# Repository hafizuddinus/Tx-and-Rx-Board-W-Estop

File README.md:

link schematic and layout of tx and rx board:
- tx schematic    : https://kicanvas.org/?repo=https%3A%2F%2Fgithub.com%2Fhafizuddinus%2FTx-and-Rx-Board-W-Estop%2Fblob%2Fmain%2FTx-Board.kicad_sch
- rx layout       : https://kicanvas.org/?repo=https%3A%2F%2Fgithub.com%2Fhafizuddinus%2FTx-and-Rx-Board-W-Estop%2Fblob%2Fmain%2FTx-Board-Copy.kicad_pcb
- rx schematic    : https://kicanvas.org/?repo=https%3A%2F%2Fgithub.com%2Fhafizuddinus%2FTx-and-Rx-Board-W-Estop%2Fblob%2Fmain%2FRx_Board-Copy.kicad_sch
- rx layout       : https://kicanvas.org/?repo=https%3A%2F%2Fgithub.com%2Fhafizuddinus%2FTx-and-Rx-Board-W-Estop%2Fblob%2Fmain%2FRx_Board-Copy.kicad_pcb

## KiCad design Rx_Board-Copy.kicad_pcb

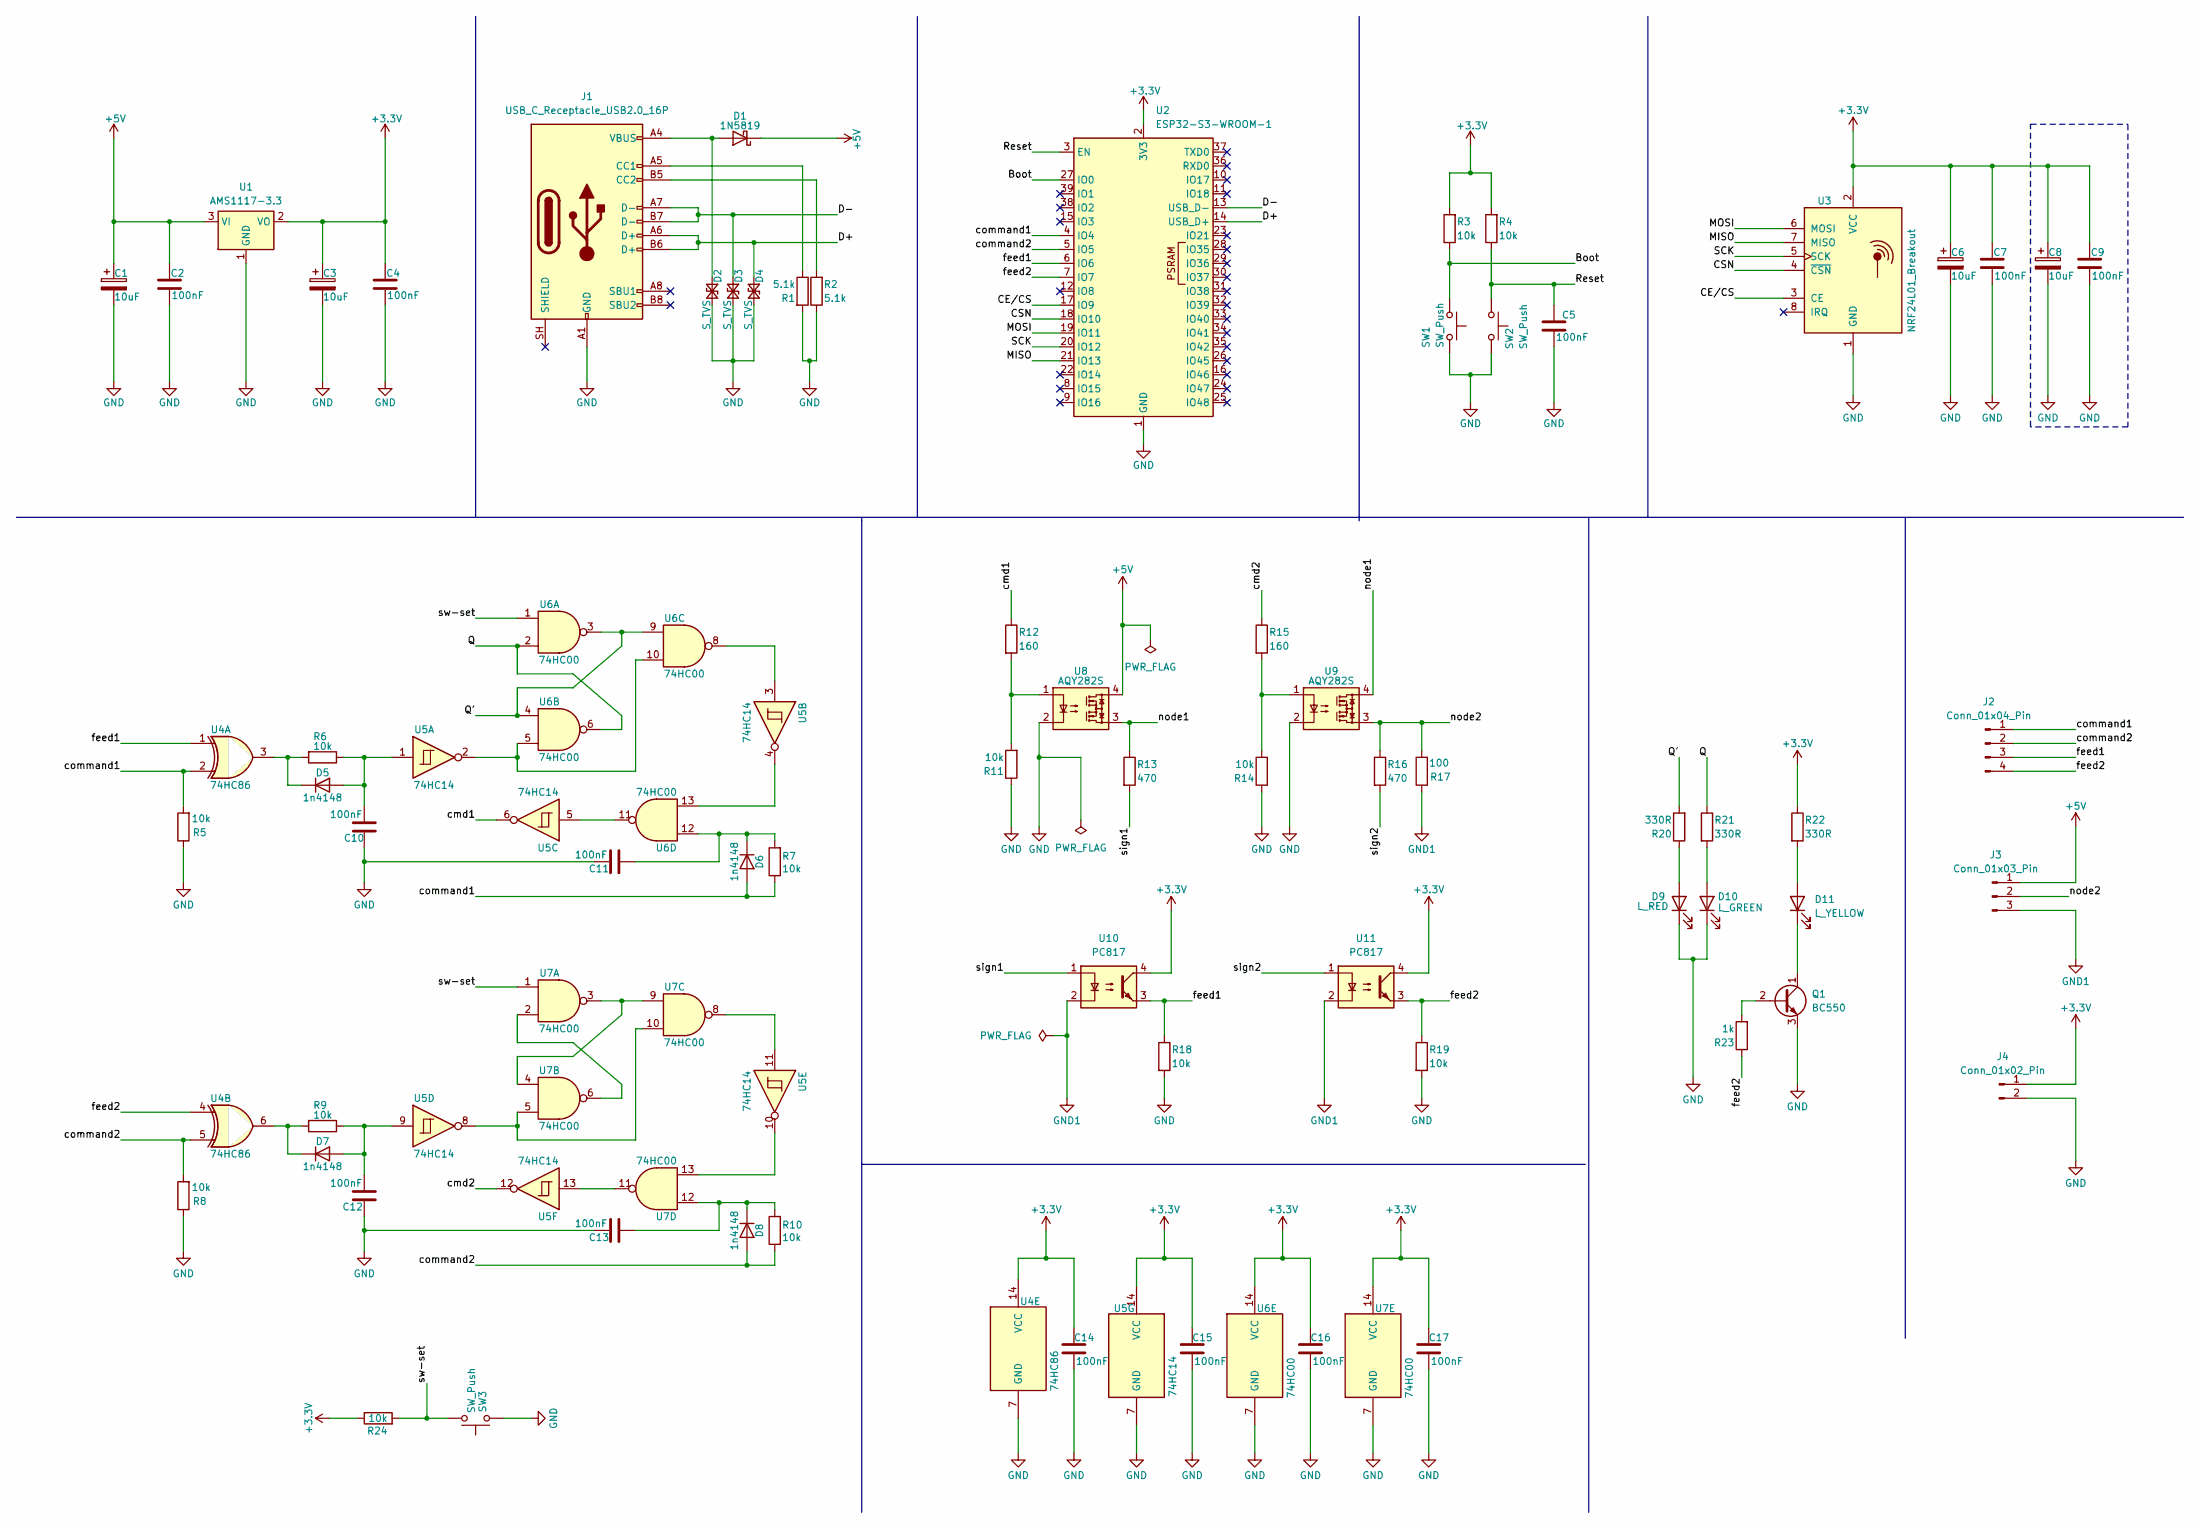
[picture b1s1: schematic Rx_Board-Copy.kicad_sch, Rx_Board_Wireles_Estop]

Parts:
C1, C3, C6, C8: 10uF; C_0805_2012Metric
C2, C4, C5, C7, C9, C10, C11, C12, C13, C14, C15, C16, C17: 100nF; C_0805_2012Metric
D1: 1N5819; D_SOD-123
D2, D3, D4: S_TVS; D_SOD-323
D5, D6, D7, D8: 1n4148; D_0805_2012Metric
D9: L_RED; LED_0805_2012Metric
D10: L_GREEN; LED_0805_2012Metric
D11: L_YELLOW; LED_0805_2012Metric
J1: USB_C_Receptacle_USB2.0_16P; USB_C_Receptacle_HRO_TYPE-C-31-M-12
J2: Conn_01x04_Pin; JST_EH_B4B-EH-A_1x04_P2.50mm_Vertical
J3: Conn_01x03_Pin; TerminalBlock_Phoenix_MKDS-1,5-3-5.08_1x03_P5.08mm_Horizont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
J4: Conn_01x02_Pin; JST_EH_S2B-EH_1x02_P2.50mm_Horizontal
Q1: BC550; TO-92_Inline
R1, R2: 5.1k; R_0805_2012Metric
R3, R4, R5, R6, R7, R8, R9, R10, R11, R14, R18, R19, R24: 10k; R_0805_2012Metric
R12, R15: 160; R_0805_2012Metric
R13, R16: 470; R_0805_2012Metric
R17: 100; R_0805_2012Metric
R20, R21, R22: 330R; R_0805_2012Metric
R23: 1k; R_0805_2012Metric
SW1, SW2: SW_Push; SW_Push_SPST_NO_Alps_SKRK
SW3: SW_Push; SW_Push_1P1T_NO_CK_KMR2
U1: AMS1117-3.3; SOT-223-3_TabPin2
U2: ESP32-S3-WROOM-1
U3: NRF24L01_Breakout; nRF24L01_Breakout
U4: 74HC86; SOIC-14_3.9x8.7mm_P1.27mm
U5: 74HC14; SOIC-14_3.9x8.7mm_P1.27mm
U6, U7: 74HC00; SOIC-14_3.9x8.7mm_P1.27mm
U8, U9: AQY282S; SO-4_4.4x4.3mm_P2.54mm
U10, U11: PC817; DIP-4_W7.62mm

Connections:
+3.3V: C3.1, C4.2, C6.1, C7.2, C8.1, C9.2, C14.2, C15.2, C16.2, C17.2, J4.1, R3.2, R4.2, R22.1, R24.1, U1.2 (VO), U2.2 (3V3), U3.2 (VCC), U4.14 (VCC), U5.14 (VCC), U6.14 (VCC), U7.14 (VCC), U10.4, U11.4
+5V: C1.1, C2.2, D1.1 (K), J3.1, U1.3 (VI), U8.4
/Boot: R3.1, SW1.1, U2.27 (IO0)
/CE/CS: U2.17 (IO9), U3.3 (CE)
/CSN: U2.18 (IO10), U3.4 (~CSN)
/D+: D4.1 (A1), J1.A6 (D+), J1.B6 (D+), U2.14 (USB_D+)
/D-: D3.1 (A1), J1.A7 (D-), J1.B7 (D-), U2.13 (USB_D-)
/MISO: U2.21 (IO13), U3.7 (MISO)
/MOSI: U2.19 (IO11), U3.6 (MOSI)
/Q: R21.1, U6.2, U6.6
/Q': R20.2, U6.3, U6.4, U6.9
/Reset: C5.2, R4.1, SW2.1, U2.3 (EN)
/SCK: U2.20 (IO12), U3.5 (SCK)
/cmd1: R12.1, U5.6
/cmd2: R15.1, U5.12
/command1: D6.2 (A), J2.1, R5.2, R7.1, U2.4 (IO4), U4.2
/command2: D8.2 (A), J2.2, R8.2, R10.1, U2.5 (IO5), U4.5
/feed1: J2.3, R18.1, U2.6 (IO6), U4.1, U10.3
/feed2: J2.4, R19.1, R23.1, U2.7 (IO7), U4.4, U11.3
/node1: R13.1, U8.3, U9.4
/node2: J3.2, R16.1, R17.2, U9.3
/sign1: R13.2, U10.1
/sign2: R16.2, U11.1
/sw-set: R24.2, SW3.2, U6.1, U7.1
GND: C1.2, C2.1, C3.2, C4.1, C5.1, C6.2, C7.1, C8.2, C9.1, C10.2, C11.2, C12.2, C13.2, C14.1, C15.1, C16.1, C17.1, D2.2 (A2), D3.2 (A2), D4.2 (A2), D9.1 (K), D10.1 (K), J1.A1 (GND), J1.A12 (GND), J1.B1 (GND), J1.B12 (GND), J4.2, Q1.3 (E), R1.2, R2.1, R5.1, R8.1, R11.1, R14.1, R18.2, R19.2, SW1.2, SW2.2, SW3.1, U1.1 (GND), U2.1 (GND), U2.40 (GND), U2.41 (GND), U3.1 (GND), U4.7 (GND), U5.7 (GND), U6.7 (GND), U7.7 (GND), U8.2, U9.2
GND1: J3.3, R17.1, U10.2, U11.2
unnamed: D1.2 (A), D2.1 (A1), J1.A4 (VBUS), J1.A9 (VBUS), J1.B4 (VBUS), J1.B9 (VBUS)
unnamed: C10.1, D5.2 (A), R6.1, U5.1
unnamed: D5.1 (K), R6.2, U4.3
unnamed: C11.1, D6.1 (K), R7.2, U6.12
unnamed: C12.1, D7.2 (A), R9.1, U5.9
unnamed: D7.1 (K), R9.2, U4.6
unnamed: C13.1, D8.1 (K), R10.2, U7.12
unnamed: D9.2 (A), R20.1
unnamed: D10.2 (A), R21.2
unnamed: D11.2 (A), R22.2
unnamed: D11.1 (K), Q1.1 (C)
unnamed: J1.A5 (CC1), R1.1
unnamed: J1.B5 (CC2), R2.2
unnamed: Q1.2 (B), R23.2
unnamed: R11.2, R12.2, U8.1
unnamed: R14.2, R15.2, U9.1
unnamed: U5.2, U6.5, U6.10
unnamed: U5.3, U6.8
unnamed: U5.4, U6.13
unnamed: U5.5, U6.11
unnamed: U5.8, U7.5, U7.10
unnamed: U5.10, U7.13
unnamed: U5.11, U7.8
unnamed: U5.13, U7.11
unnamed: U7.2, U7.6
unnamed: U7.3, U7.4, U7.9

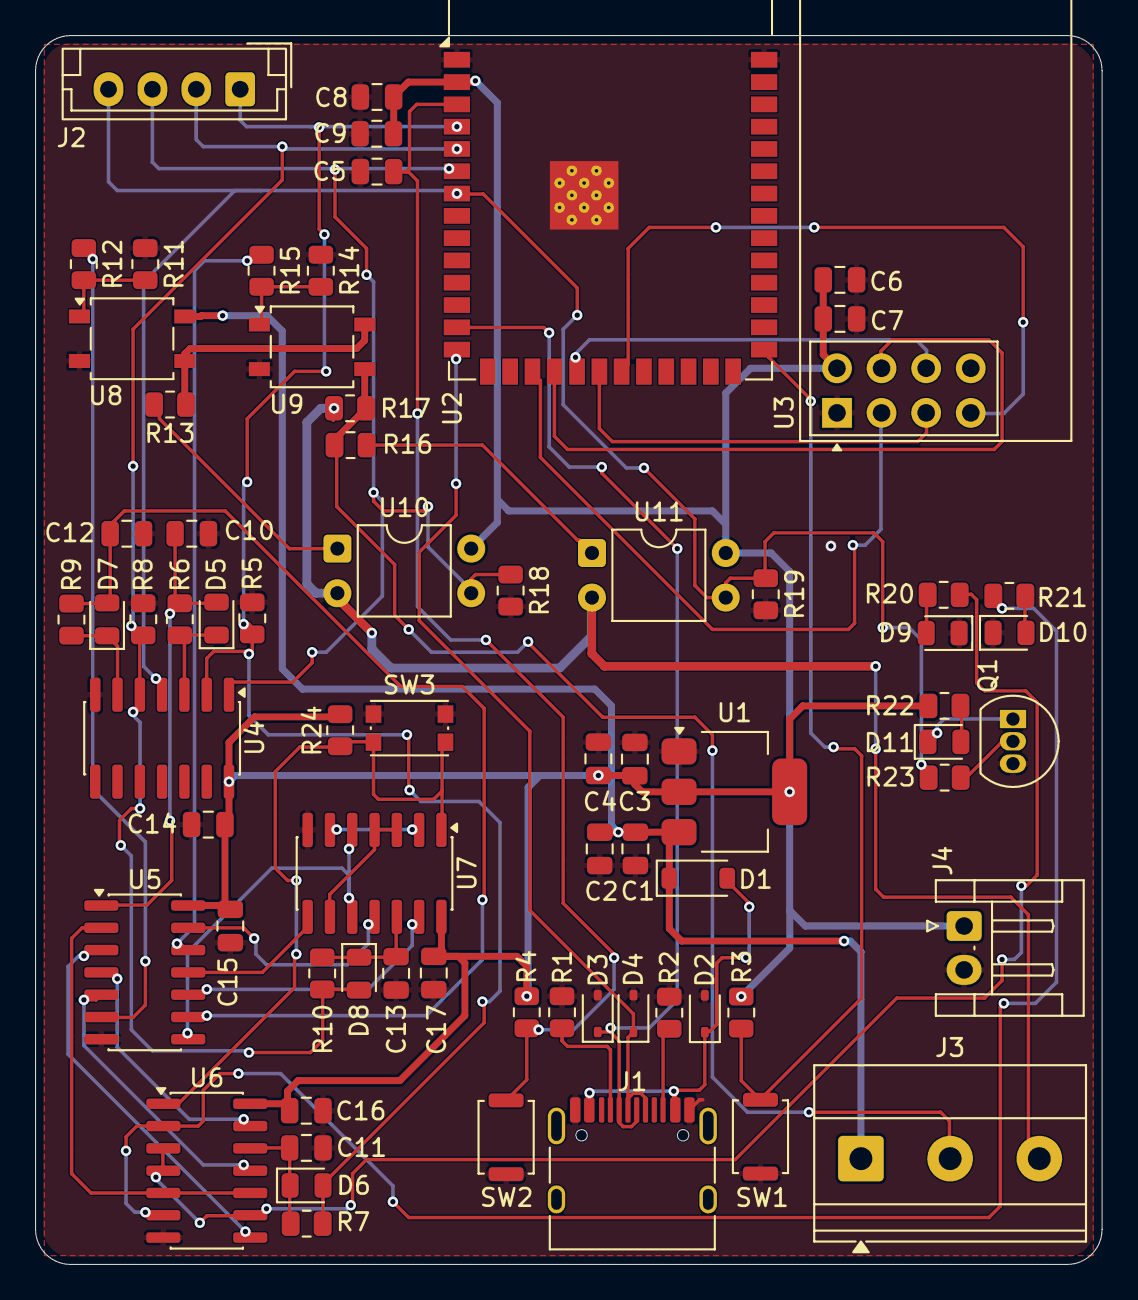
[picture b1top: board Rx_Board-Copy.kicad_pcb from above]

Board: 2 copper layers, 60.8 x 70.0 mm, 71 parts (0 on the bottom side), 52 nets.

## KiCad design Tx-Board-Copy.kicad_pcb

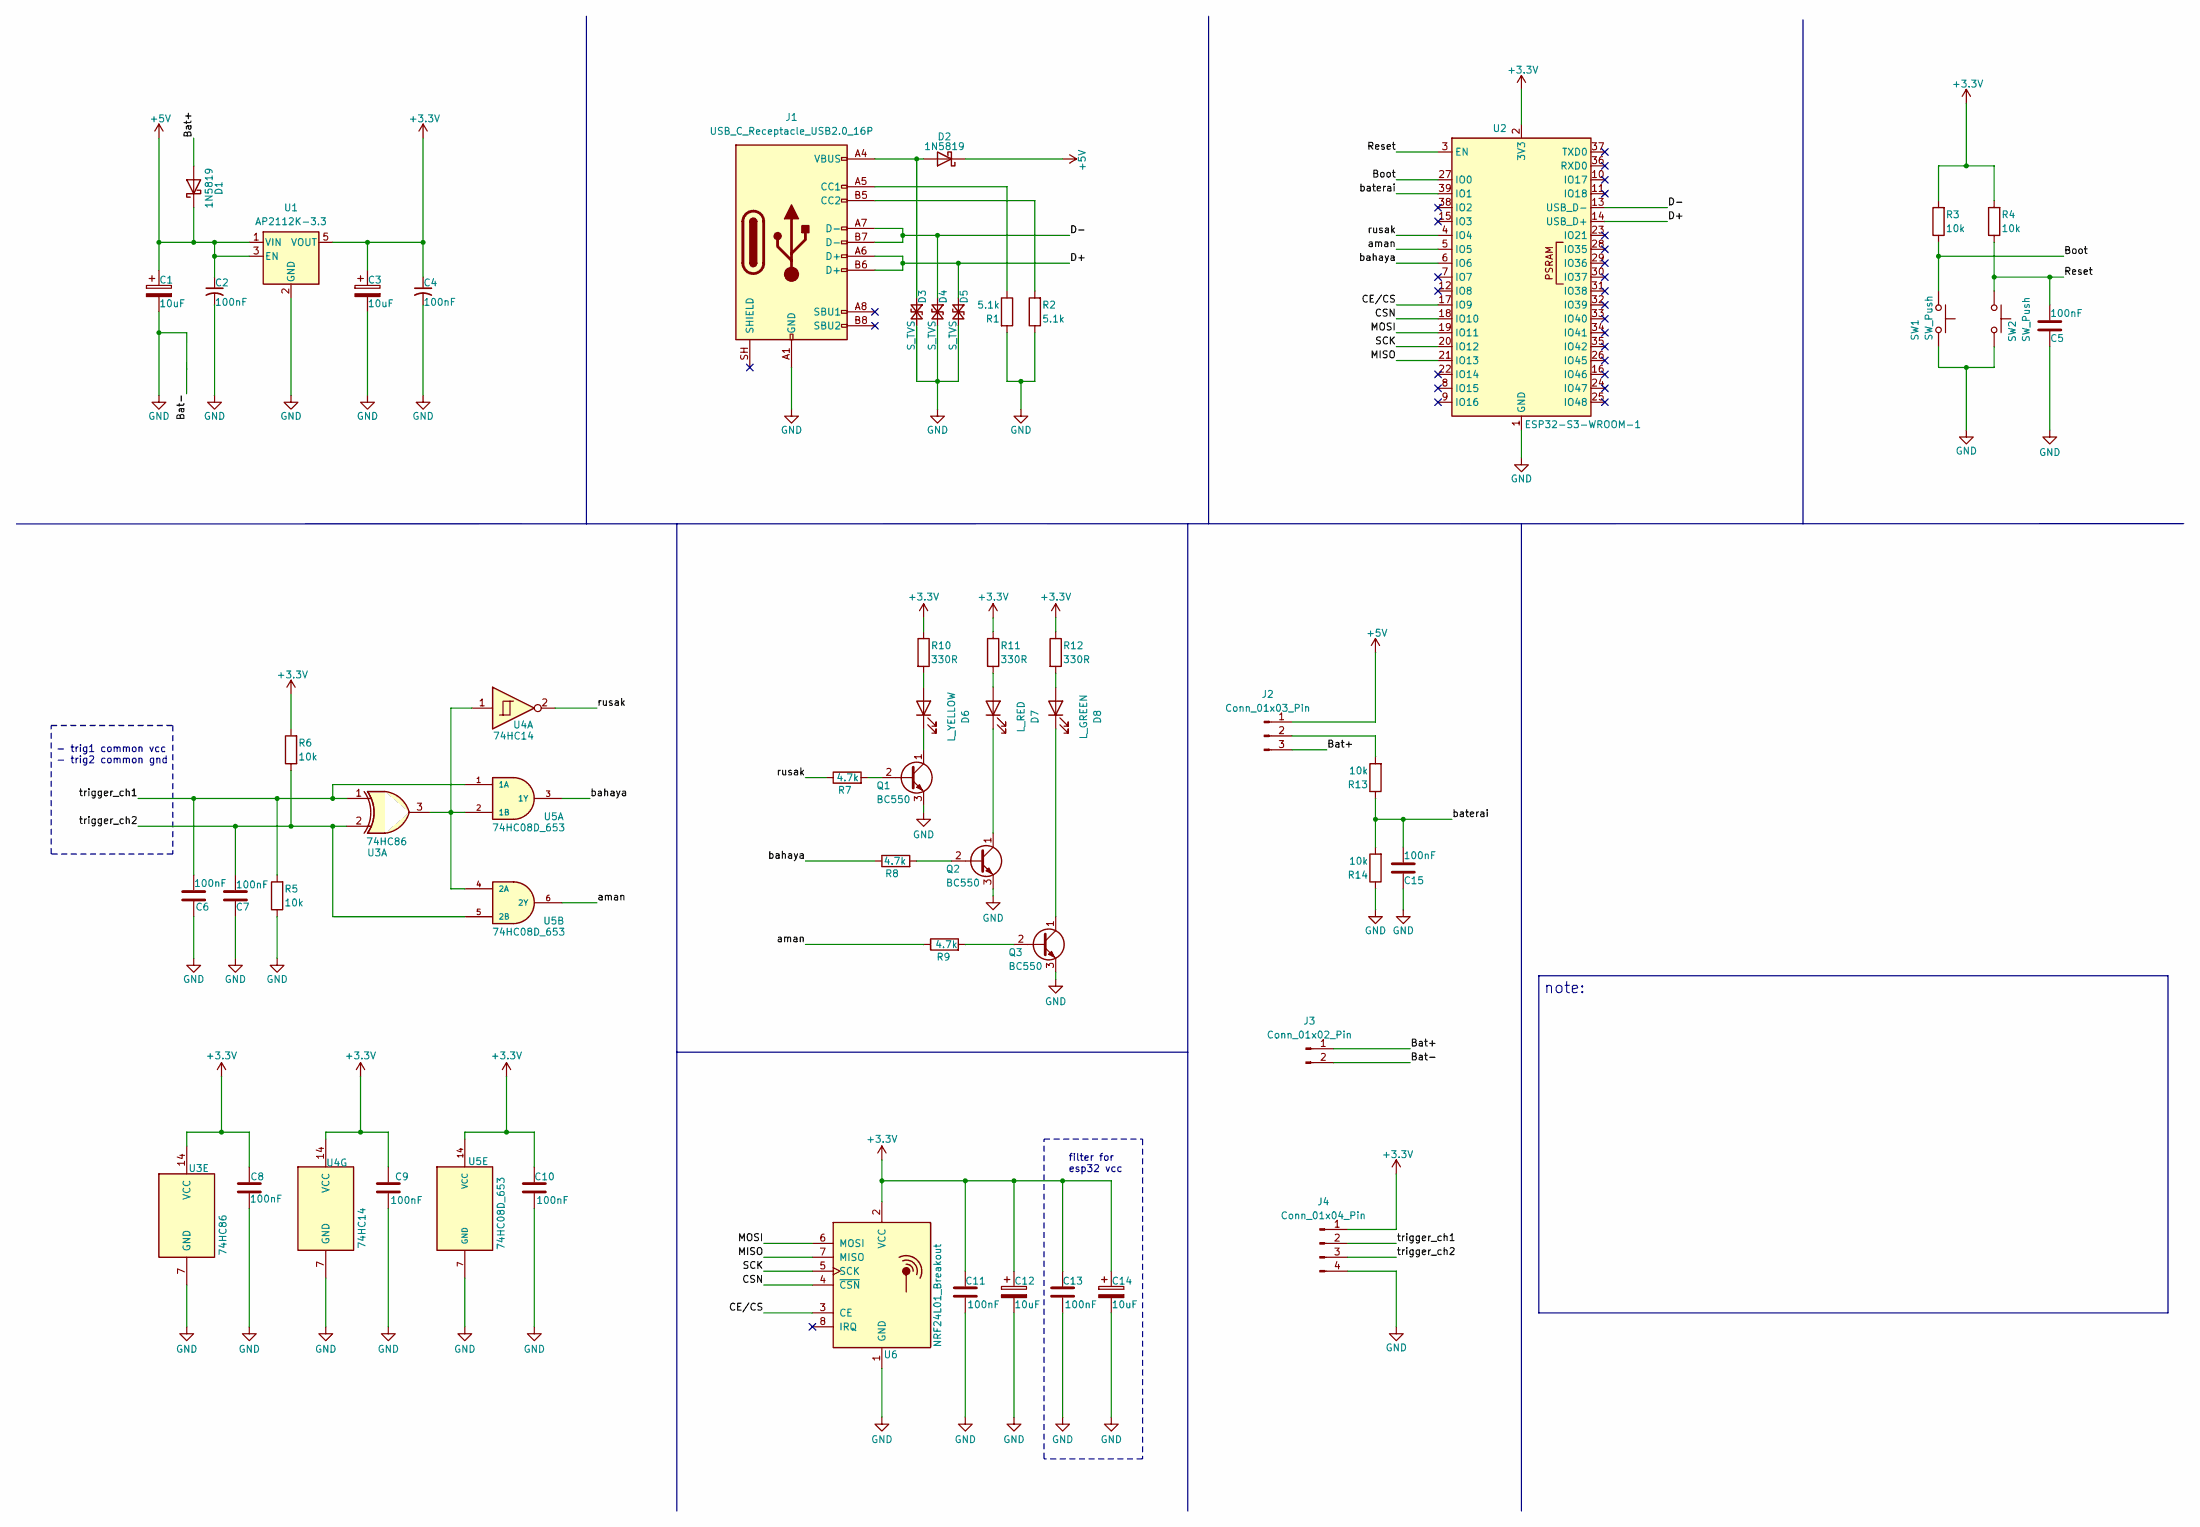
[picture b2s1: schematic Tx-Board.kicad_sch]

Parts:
C1, C3, C12, C14: 10uF; C_0805_2012Metric
C2, C4, C5, C6, C7, C8, C9, C10, C11, C13, C15: 100nF; C_0805_2012Metric
D1, D2: 1N5819; D_SOD-123
D3, D4, D5: S_TVS; D_SOD-323
D6: L_YELLOW; LED_0805_2012Metric
D7: L_RED; LED_0805_2012Metric
D8: L_GREEN; LED_0805_2012Metric
J1: USB_C_Receptacle_USB2.0_16P; USB_C_Receptacle_HRO_TYPE-C-31-M-12
J2: Conn_01x03_Pin; PinHeader_1x03_P2.54mm_Vertical
J3: Conn_01x02_Pin; JST_EH_B2B-EH-A_1x02_P2.50mm_Vertical
J4: Conn_01x04_Pin; JST_EH_B4B-EH-A_1x04_P2.50mm_Vertical
Q1, Q2, Q3: BC550; TO-92_Inline
R1, R2: 5.1k; R_0805_2012Metric
R3, R4, R5, R6, R13, R14: 10k; R_0805_2012Metric
R7, R8, R9: 4.7k; R_0805_2012Metric
R10, R11, R12: 330R; R_0805_2012Metric
SW1, SW2: SW_Push; SW_Push_SPST_NO_Alps_SKRK
U1: AP2112K-3.3; SOT-23-5
U2: ESP32-S3-WROOM-1
U3: 74HC86; SOIC-14_3.9x8.7mm_P1.27mm
U4: 74HC14; SOIC-14_3.9x8.7mm_P1.27mm
U5: 74HC08D_653; SOIC-14_3.9x8.7mm_P1.27mm; MPN 74HC08D,653
U6: NRF24L01_Breakout; nRF24L01_Breakout

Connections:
+3.3V: C3.1, C4.1, C8.2, C9.2, C10.2, C11.2, C12.1, C13.2, C14.1, J4.1, R3.2, R4.2, R6.2, R10.1, R11.1, R12.1, U1.5 (VOUT), U2.2 (3V3), U3.14 (VCC), U4.14 (VCC), U5.14 (VCC), U6.2 (VCC)
+5V: C1.1, C2.1, D1.1 (K), D2.1 (K), J2.1, U1.1 (VIN), U1.3 (EN)
/Bat+: D1.2 (A), J2.3, J3.1
/Boot: R3.1, SW1.1, U2.27 (IO0)
/CE/CS: U2.17 (IO9), U6.3 (CE)
/CSN: U2.18 (IO10), U6.4 (~CSN)
/D+: D5.1 (A1), J1.A6 (D+), J1.B6 (D+), U2.14 (USB_D+)
/D-: D4.1 (A1), J1.A7 (D-), J1.B7 (D-), U2.13 (USB_D-)
/MISO: U2.21 (IO13), U6.7 (MISO)
/MOSI: U2.19 (IO11), U6.6 (MOSI)
/Reset: C5.1, R4.1, SW2.1, U2.3 (EN)
/SCK: U2.20 (IO12), U6.5 (SCK)
/aman: R9.1, U2.5 (IO5), U5.6 (2Y)
/bahaya: R8.1, U2.6 (IO6), U5.3 (1Y)
/baterai: C15.1, R13.1, R14.2, U2.39 (IO1)
/rusak: R7.1, U2.4 (IO4), U4.2
/trigger_ch1: C6.1, J4.2, R5.2, U3.1, U5.1 (1A)
/trigger_ch2: C7.1, J4.3, R6.1, U3.2, U5.5 (2B)
GND: C1.2, C2.2, C3.2, C4.2, C5.2, C6.2, C7.2, C8.1, C9.1, C10.1, C11.1, C12.2, C13.1, C14.2, C15.2, D3.2 (A2), D4.2 (A2), D5.2 (A2), J1.A1 (GND), J1.A12 (GND), J1.B1 (GND), J1.B12 (GND), J3.2, J4.4, Q1.3 (E), Q2.3 (E), Q3.3 (E), R1.2, R2.1, R5.1, R14.1, SW1.2, SW2.2, U1.2 (GND), U2.1 (GND), U2.40 (GND), U2.41 (GND), U3.7 (GND), U4.7 (GND), U5.7 (GND), U6.1 (GND)
unnamed: D2.2 (A), D3.1 (A1), J1.A4 (VBUS), J1.A9 (VBUS), J1.B4 (VBUS), J1.B9 (VBUS)
unnamed: D6.2 (A), R10.2
unnamed: D6.1 (K), Q1.1 (C)
unnamed: D7.2 (A), R11.2
unnamed: D7.1 (K), Q2.1 (C)
unnamed: D8.2 (A), R12.2
unnamed: D8.1 (K), Q3.1 (C)
unnamed: J1.A5 (CC1), R1.1
unnamed: J1.B5 (CC2), R2.2
unnamed: J2.2, R13.2
unnamed: Q1.2 (B), R7.2
unnamed: Q2.2 (B), R8.2
unnamed: Q3.2 (B), R9.2
unnamed: U3.3, U4.1, U5.2 (1B), U5.4 (2A)

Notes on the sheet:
filter for esp32 vcc
note:
- trig1 common vcc - trig2 common gnd

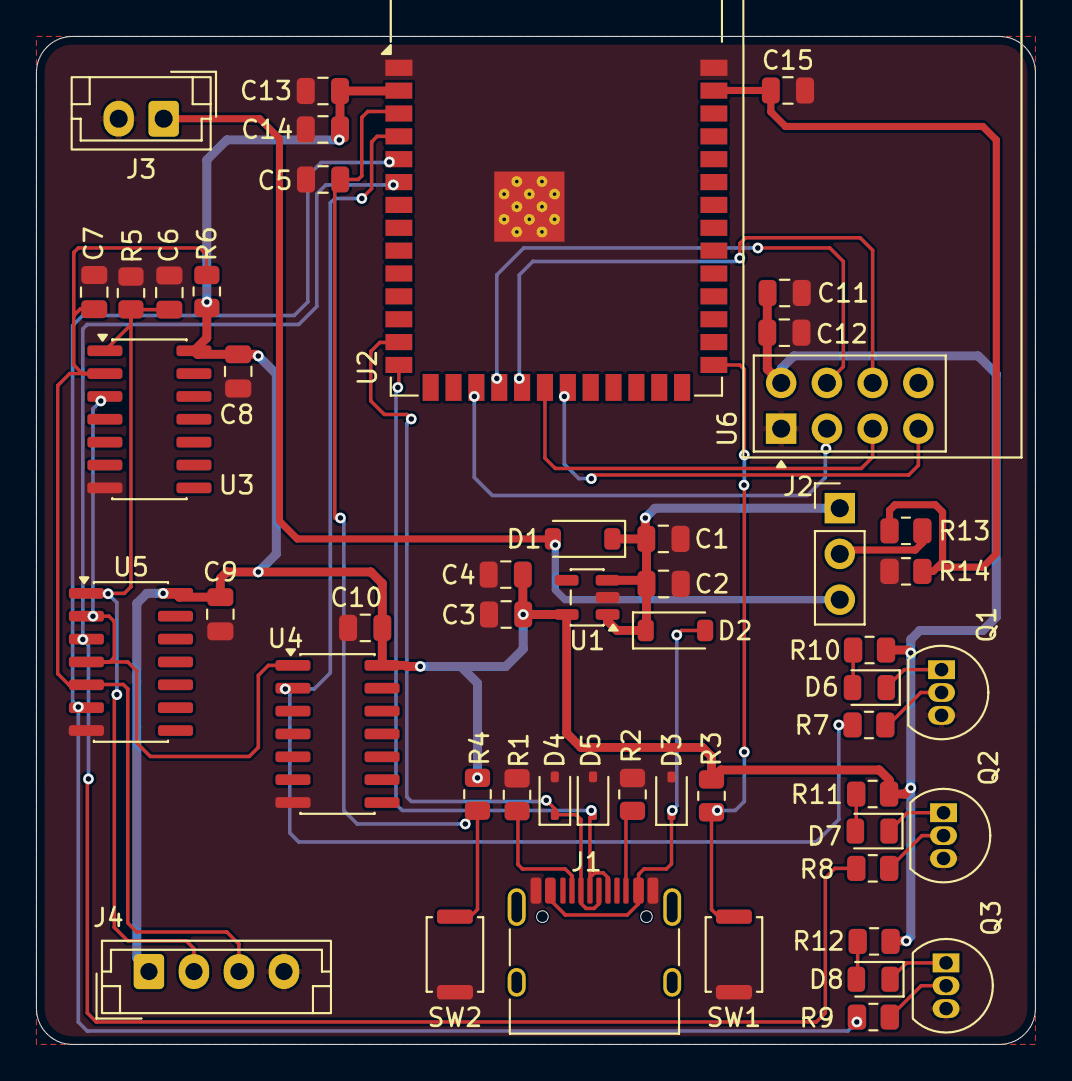
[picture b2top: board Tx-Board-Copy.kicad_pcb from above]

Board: 2 copper layers, 55.5 x 56.0 mm, 52 parts (0 on the bottom side), 33 nets.
